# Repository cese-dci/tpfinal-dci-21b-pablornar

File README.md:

## Trabajo práctico final de la asignatura DCI ##
Este repositorio contiene el trabajo práctico final para la asignatura de Diseño de Circuitos Impresos de la carrera de posgrado de FIUBA.

* Autor: Narvaez Pablo
* Título corto del trabajo:  Generación y Adquisición de seniales de Rf de baja frecuencia
* Descripción:  El presente proyecto tiene como objetivo el desarrollo de las placas para un equipo (prototipo) que permita medir y analizar señales electrónicas en el
dominio del tiempo y en el de la frecuencia.

## Licencia de este trabajo ##
Licencia: GPLv3
Y además colcar el archivo de texto de la misma en el directorio raíz.
Para este TP se pide que la licencia sea de hardware abierto.
Ver la sección "What license should I use?": https://www.oshwa.org/faq/

## Estructura del TP FINAL ##

Se propone y se pide utilizar la siguiente estructura.

* doc: Toda la información sobre el circuito, principalmente de autoría o procesamiento propio. Por ejemplo:
  * Notas de ingeniería propias.
  * Notas de aplicación propias.
  * Estudios previos, estado del arte, resumen de las investigaciones.
  * Notas con cálculos.
  * Dibujos adicionales.
  * Fotos de los prototipos.
  * Presupuestos, cotizaciones.
* info: Toda la iformación recolectada, principalmente de terceros, como por ejemplo:
  * Hojas de datos.
  * Notas de aplicación.
  * Info de productos comerciales.
  * Info en internet.
* pcb: Archivos de diseño esquemático y pcb.

Dependiendo la magnitud del proyecto, tendremos más o menos información en estos directorios. 
Revisar los README.md en cada directorio para conocer las pautas de cada uno para este TP.

NOTA: El alumno puede y debe borrar de este archivo todo lo que considere necesario, por ejemplo las aclaraciones del docente y esta misma nota.

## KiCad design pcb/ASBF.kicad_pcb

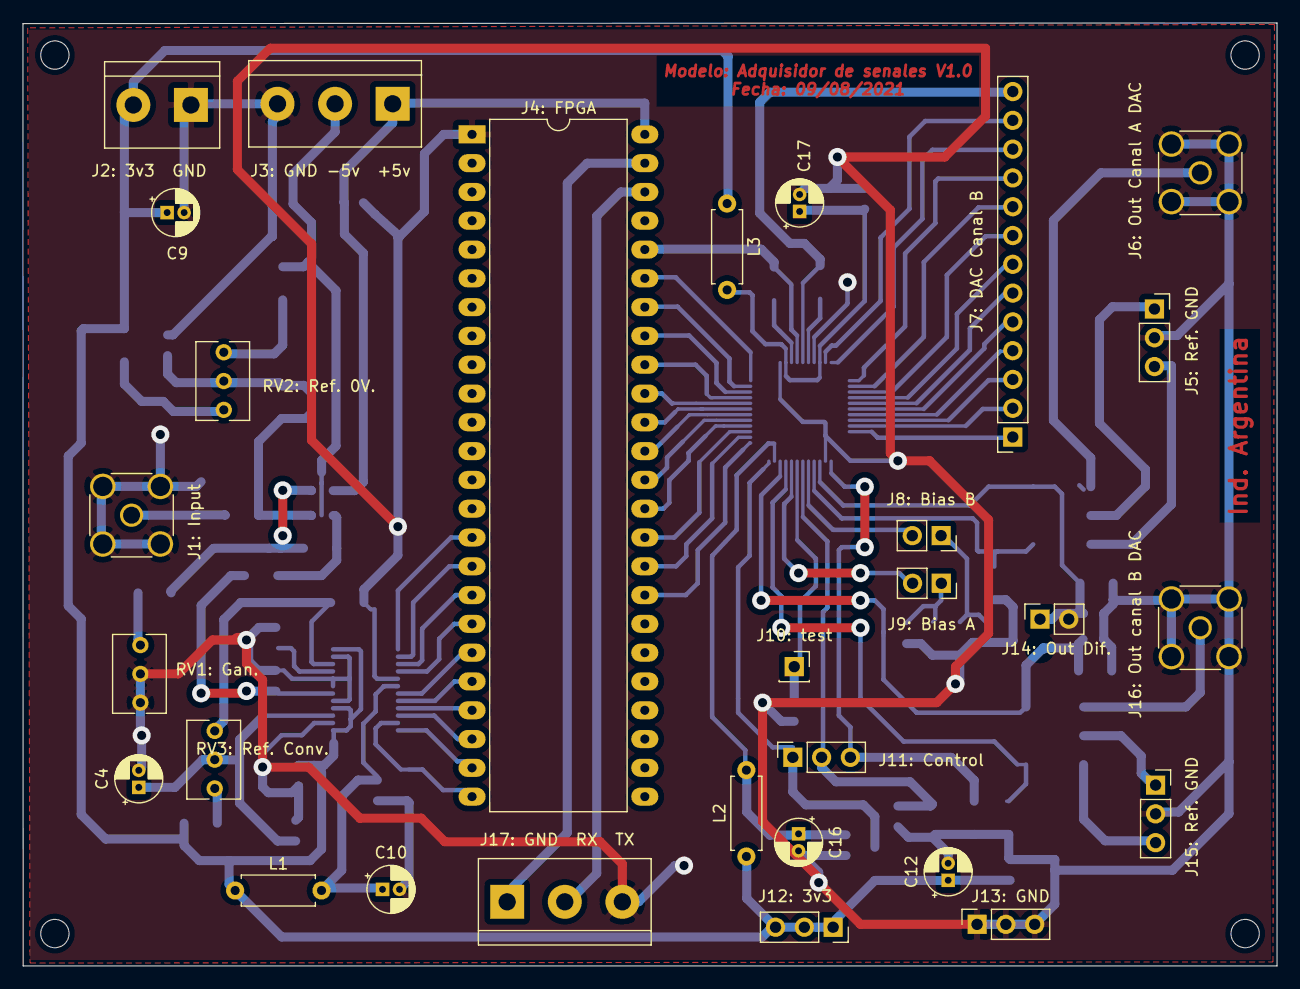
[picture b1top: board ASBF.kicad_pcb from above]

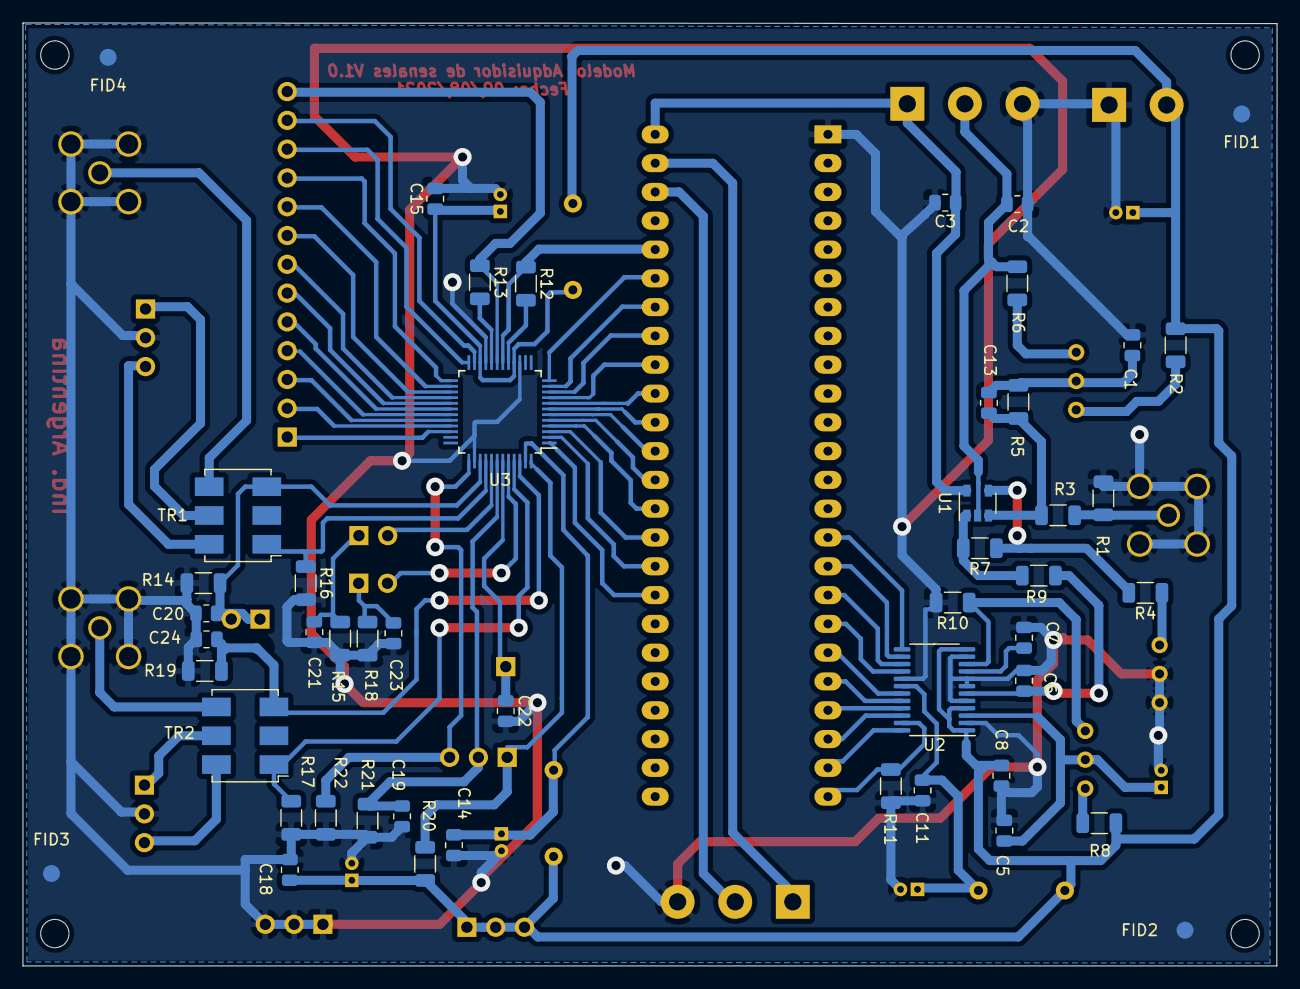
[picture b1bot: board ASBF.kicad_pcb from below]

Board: 2 copper layers, 110.6 x 83.2 mm, 82 parts (51 on the bottom side), 78 nets.

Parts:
C1: 0.33uF; R_0805_2012Metric
C2, C3, C5, C7, C11: 0.1uF; R_0805_2012Metric
C4, C9, C10, C16, C17: 10uF; CP_Radial_D4.0mm_P1.50mm
C6: 10pF; R_0805_2012Metric
C8: 0,1 uF; R_0805_2012Metric
C12: 1uF; CP_Radial_D4.0mm_P1.50mm
C13: 1nf; R_0805_2012Metric
C14, C15, C18, C19, C20, C21, C22, C23, C24: 100nF; R_0805_2012Metric
FID1, FID2, FID3, FID4: Fiducial; Fiducial_1.5mm_Mask3mm
H1, H2, H3, H4: MountingHole; MountingHole_2.5mm
J1: Input , J6: Out Canal A DAC, J16: Out canal B DAC: Conn_01x02; SMA_Amphenol_132134-16_Vertical
J2: 3v3  GND: Screw_Terminal_01x02; TerminalBlock_bornier-2_P5.08mm
J3: GND -5v  +5v, J17: GND  RX  TX: Screw_Terminal_01x03; TerminalBlock_bornier-3_P5.08mm
J4: FPGA: Conn_02x24_Counter_Clockwise; DIP-48_W15.24mm_LongPads
J5: Ref. GND, J11: Control, J12: 3v3, J13: GND, J15: Ref. GND: Conn_01x03; PinSocket_1x03_P2.54mm_Vertical
J7: DAC Canal B: Conn_01x13; PinSocket_1x13_P2.54mm_Vertical
J8: Bias B, J9: Bias A, J14: Out Dif.: Conn_01x02; PinSocket_1x02_P2.54mm_Vertical
J10: test: Conn_01x01; PinSocket_1x01_P2.54mm_Vertical
L1: 100uh; R_Axial_DIN0207_L6.3mm_D2.5mm_P7.62mm_Horizontal
L2, L3: 47uh; R_Axial_DIN0207_L6.3mm_D2.5mm_P7.62mm_Horizontal
R1: 100; R_1206_3216Metric
R2: 1k; R_1206_3216Metric
R3: 240; R_1206_3216Metric
R4: 12; R_1206_3216Metric
R5: 2000; R_1206_3216Metric
R6, R11: 4.7k; R_1206_3216Metric
R7: 200; R_1206_3216Metric
R8, R10: 1; R_1206_3216Metric
R9: 22; R_1206_3216Metric
R12, R13: 0; R_1206_3216Metric
R14, R19: 50; R_1206_3216Metric
R15, R18: 2K; R_1206_3216Metric
R16, R17: 25; R_1206_3216Metric
R20, R21, R22: 3k3; R_1206_3216Metric
RV1: Gan.: 10; Potentiometer_Bourns_3266Y_Vertical
RV2: Ref. 0V., RV3: Ref. Conv.: 1k; Potentiometer_Bourns_3266Y_Vertical
TR1, TR2: ADT4-6T; Mini-Circuits_CD637_H5.23mm
U1: LMH6702MF; SOT-23-5
U2: ADC080200; TSSOP-24_4.4x7.8mm_P0.65mm
U3: DAC5662A; TQFP-48_7x7mm_P0.5mm

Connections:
+3V3: C8.2, C9.1, C12.1, C18.1, J2: 3v3 GND.2, J12: 3v3.1, J12: 3v3.2, J12: 3v3.3, L1.1, L2.1, L3.1, R2.2, R8.1, R20.1, U2.1, U2.4, U2.12
+5V: C3.1, J3: GND -5v +5v.1, J4: FPGA.48, U1.5
-5V: C2.1, J3: GND -5v +5v.2, R6.1, U1.2
/ADC/CLK: J4: FPGA.23, U2.24
/ADC/D0: J4: FPGA.22, U2.22
/ADC/D1: J4: FPGA.21, U2.21
/ADC/D2: J4: FPGA.20, U2.20
/ADC/D3: J4: FPGA.19, U2.19
/ADC/D4: J4: FPGA.18, U2.16
/ADC/D5: J4: FPGA.17, U2.15
/ADC/D7: J4: FPGA.16, U2.14
/ADC/D8: J4: FPGA.15, U2.13
/ADC/PWR_DWN: J4: FPGA.24, R11.1, U2.23
/DAC/ClkA: J4: FPGA.44, R12.1, U3.18
/DAC/DA0: J4: FPGA.43, U3.12
/DAC/DA1: J4: FPGA.42, U3.11
/DAC/DA2: J4: FPGA.41, U3.10
/DAC/DA3: J4: FPGA.40, U3.9
/DAC/DA4: J4: FPGA.39, U3.8
/DAC/DA5: J4: FPGA.38, U3.7
/DAC/DA6: J4: FPGA.37, U3.6
/DAC/DA7: J4: FPGA.36, U3.5
/DAC/DA8: J4: FPGA.35, U3.4
/DAC/DA9: J4: FPGA.34, U3.3
/FPGA_Conector/A14: J4: FPGA.33, U3.2
/FPGA_Conector/B15: J4: FPGA.32, U3.1
GND: C1.1, C2.2, C3.2, C4.2, C5.2, C6.2, C7.2, C8.1, C9.2, C10.2, C11.2, C12.2, C14.2, C15.2, C16.2, C17.2, C18.2, C19.2, C20.2, C21.1, C22.2, C23.2, C24.2, J1: Input.2, J2: 3v3 GND.1, J3: GND -5v +5v.3, J4: FPGA.1, J5: Ref. GND.2, J6: Out Canal A DAC.2, J13: GND.1, J13: GND.2, J13: GND.3, J15: Ref. GND.2, J16: Out canal B DAC.2, J17: GND RX TX.3, R1.1, R10.2, R11.2, R14.2, R15.1, R16.2, R17.2, R18.2, R19.2, R21.2, R22.2, RV1: Gan..1, RV1: Gan..2, U2.2, U2.5, U2.7, U2.8, U2.11, U2.17, U3.15, U3.21, U3.38
unnamed: C1.2, C13.1, R5.2, RV2: Ref. 0V..2
unnamed: C4.1, C5.1, RV3: Ref. Conv..2, U2.3
unnamed: C6.1, R9.2, U2.6
unnamed: C7.1, U2.9
unnamed: C10.1, C11.1, L1.2, U2.18
unnamed: C13.2, R3.2, R5.1, U1.3
unnamed: C14.1, C16.1, L2.2, U3.47
unnamed: C15.1, C17.1, L3.2, U3.16, U3.22
unnamed: C19.1, J11: Control.2, R21.1, U3.42
unnamed: C20.1, J14: Out Dif..1, R14.1, TR1.3, U3.39
unnamed: C21.2, J8: Bias B.1, R15.2
unnamed: C22.1, J10: test.1, U3.43
unnamed: C23.1, J9: Bias A.1, R18.1
unnamed: C24.1, J14: Out Dif..2, R19.1, TR2.3, U3.46
unnamed: J1: Input.1, R1.2, R3.1
unnamed: J5: Ref. GND.1, TR1.5
unnamed: J5: Ref. GND.3, TR1.6
unnamed: J6: Out Canal A DAC.1, TR1.4
unnamed: J7: DAC Canal B.1, U3.34
unnamed: J7: DAC Canal B.2, U3.33
unnamed: J7: DAC Canal B.3, U3.32
unnamed: J7: DAC Canal B.4, U3.31
unnamed: J7: DAC Canal B.5, U3.30
unnamed: J7: DAC Canal B.6, U3.29
unnamed: J7: DAC Canal B.7, U3.28
unnamed: J7: DAC Canal B.8, U3.27
unnamed: J7: DAC Canal B.9, U3.26
unnamed: J7: DAC Canal B.10, U3.25
unnamed: J7: DAC Canal B.11, U3.24
unnamed: J7: DAC Canal B.12, U3.23
unnamed: J7: DAC Canal B.13, R13.1, U3.19
unnamed: J8: Bias B.2, U3.41
unnamed: J9: Bias A.2, U3.44
unnamed: J11: Control.1, R20.2, U3.48
unnamed: J11: Control.3, R22.1, U3.37
unnamed: J15: Ref. GND.1, TR2.5
unnamed: J15: Ref. GND.3, TR2.6
unnamed: J16: Out canal B DAC.1, TR2.4
unnamed: J4: FPGA.47, J17: GND RX TX.1
unnamed: J4: FPGA.46, J17: GND RX TX.2
unnamed: R2.1, RV2: Ref. 0V..1
unnamed: R4.1, RV1: Gan..3
unnamed: R4.2, R7.1, U1.4
unnamed: R6.2, RV2: Ref. 0V..3
unnamed: R7.2, R9.1, U1.1
unnamed: R8.2, RV3: Ref. Conv..1
unnamed: R10.1, RV3: Ref. Conv..3, U2.10
unnamed: R12.2, U3.17
unnamed: R13.2, U3.20
unnamed: R16.1, TR1.1, U3.40
unnamed: R17.1, TR2.1, U3.45

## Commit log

2021-06-27 Primer commit
2021-06-27 agregado de fotos
2021-06-27 agregado de datasheets
2021-07-05 version 1.0
2021-07-12 1ra correcciones segun revision 1ra
2021-07-26 Realizado de PCB
2021-07-26 agregado de 3d adt
2021-07-27 agregado de 3d sma
2021-08-04 pcb v2.1
2021-08-10 version 2.0
2021-08-16 correcciones agregadas
2021-08-16 agregado de pdf
